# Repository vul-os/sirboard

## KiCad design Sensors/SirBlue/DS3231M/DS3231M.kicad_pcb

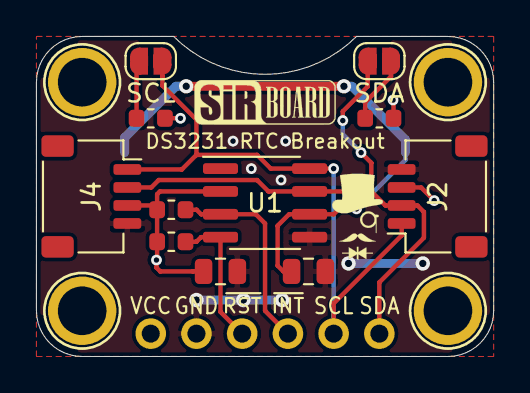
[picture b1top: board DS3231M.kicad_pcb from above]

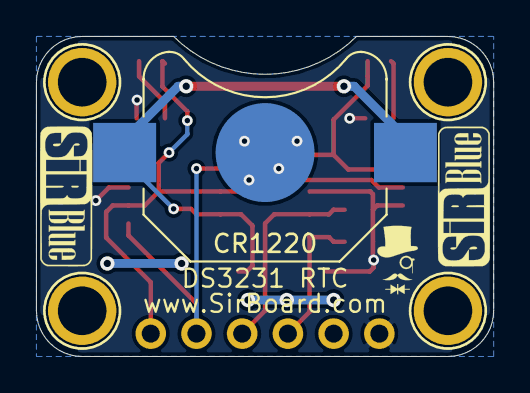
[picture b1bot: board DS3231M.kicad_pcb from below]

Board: 2 copper layers, 25.4 x 17.8 mm, 17 parts (2 on the bottom side), 9 nets.

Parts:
C1: 10uF; C_0805_2012Metric
C2: 1uF; C_0805_2012Metric
CR1220: CR1220; BatteryHolder_Keystone_3000_1x12mm
H1, H2, H3, H4: MountingHole; MountingHole_M2.5_SirBoard
J1: Conn_01x06; PinHeader_1x06_P2.54mm_Vertical
J2, J4: Conn_01x04; JST_SH_SM04B-SRSS-TB_1x04-1MP_P1.00mm_Horizontal
R1, R2: 4.7k; R_0603_1608Metric
R3, R4: 10k; R_0603_1608Metric
SCL: SolderJumper_2_Open; SolderJumper-2_P1.3mm_Open_RoundedPad1.0x1.5mm
SDA: SolderJumper_2_Open; SolderJumper-2_P1.3mm_Open_RoundedPad1.0x1.5mm
U1: DS3231MZ; SOIC-8_3.9x4.9mm_P1.27mm

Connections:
GND: C1.2, C2.2, CR1220.2, J1.2, J2.4, J4.4, U1.5
unnamed: R1.2, SCL.2
unnamed: R2.2, SDA.2
RST: J1.3, R3.2, U1.4
SCL: J1.5, J2.1, J4.1, SCL.1, U1.8
SDA: J1.6, J2.2, J4.2, SDA.1, U1.7
SQW: J1.4, R4.2, U1.3
VBAT: C2.1, CR1220.1, U1.6
VCC: C1.1, J1.1, J2.3, J4.3, R1.1, R2.1, R3.1, R4.1, U1.2

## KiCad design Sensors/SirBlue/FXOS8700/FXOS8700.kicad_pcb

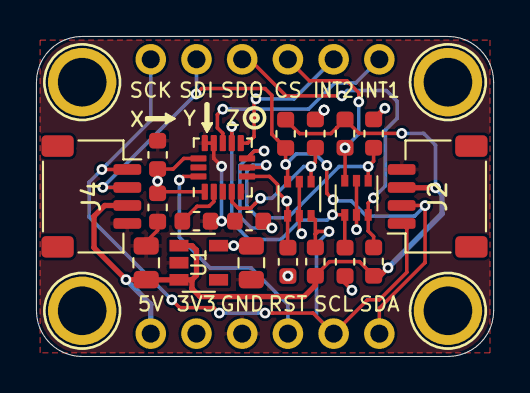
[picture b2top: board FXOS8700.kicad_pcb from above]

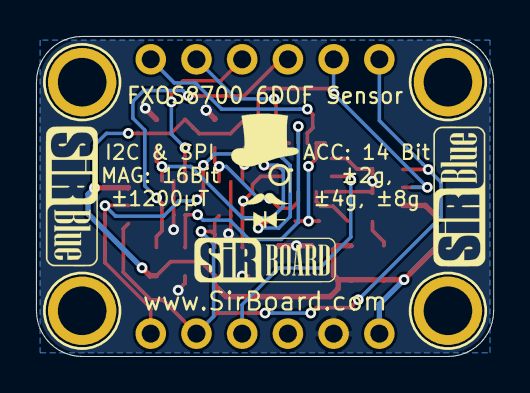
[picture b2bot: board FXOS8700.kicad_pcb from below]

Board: 2 copper layers, 25.4 x 17.8 mm, 26 parts (2 on the bottom side), 16 nets.

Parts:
C1, C4: 10uF; C_0805_2012Metric
C2, C3, C5, C6: 100nF; C_0603_1608Metric
H1, H2, H3, H4: MountingHole; MountingHole_M2.5_SirBoard
J1, J3: Conn_01x06; PinHeader_1x06_P2.54mm_Vertical
J2, J4: Conn_01x04; JST_SH_SM04B-SRSS-TB_1x04-1MP_P1.00mm_Horizontal
Q1, Q2: BSS138DW; SOT-363_SC-70-6
R1, R2, R3, R4, R5, R6, R7, R8: 10K; R_0603_1608Metric
U1: AP2127K-3.3; SOT-23-5
U2: FXOS8700; QFN-COL-16-P=0.5

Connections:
3V3: C3.1, C4.1, C6.1, J1.2, Q1.2, Q1.5, Q2.2, Q2.5, R1.2, R3.2, R5.2, R7.2, U1.5, U2.1, U2.14
5V: C1.1, J1.1, J2.3, J4.3, R2.1, R4.1, R6.1, R8.1, U1.1, U1.3
CS_3V3: Q1.4, R3.1, U2.10
CS_5V: J3.4, Q1.3, R4.2
GND: C1.2, C2.2, C3.2, C4.2, C5.2, C6.2, J1.3, J2.4, J4.4, U1.2, U2.5, U2.12, U2.13
INT1: J3.6, U2.11
INT2: J3.5, U2.9
unnamed: C2.1, U2.2
unnamed: C5.1, U2.8
RST: J1.4, U2.16
SCL_3V3: Q2.1, R5.1, U2.4
SCL_5V: J1.5, J2.1, J3.1, J4.1, Q2.6, R6.2
SDA_3V3: Q2.4, R7.1, U2.6
SDA_5V: J1.6, J2.2, J3.2, J4.2, Q2.3, R8.2
SDO_3V3: Q1.1, R1.1, U2.7
SDO_5V: J3.3, Q1.6, R2.2

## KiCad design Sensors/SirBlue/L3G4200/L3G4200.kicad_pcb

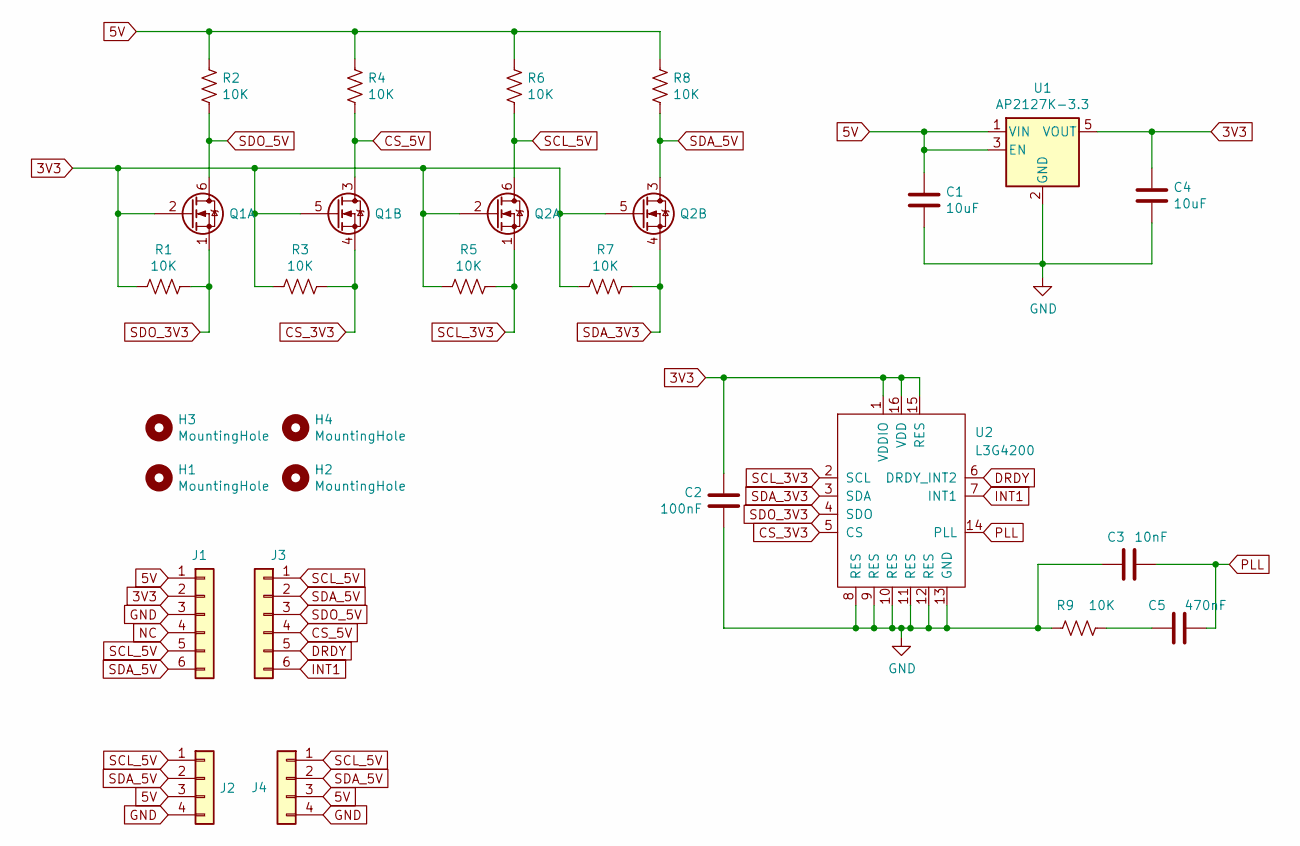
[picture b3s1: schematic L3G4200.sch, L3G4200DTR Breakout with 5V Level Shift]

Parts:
C1, C4: 10uF; C_0805_2012Metric; Part C95841
C2: 100nF; C_0603_1608Metric; Part C42998
C3: 10nF; C_0603_1608Metric; Part C100042
C5: 470nF; C_0603_1608Metric; Part C326968
H1, H2, H3, H4: MountingHole; MountingHole_M2.5_SirBoard
J1, J3: Conn_01x06; PinHeader_1x06_P2.54mm_Vertical
J2, J4: Conn_01x04; SirBlue_Connector; Part C160404
Q1, Q2: BSS138DW; SOT-363_SC-70-6
R1, R2, R3, R4, R5, R6, R7, R8, R9: 10K; R_0603_1608Metric; Part C99198
U1: AP2127K-3.3; SOT-23-5; Part C156285
U2: L3G4200; LGA-16_4x4mm_P0.65mm_LayoutBorder4x4y; Part C26444

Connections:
3V3: C2.1, C4.1, J1.2, Q1.2 (G), Q1.5 (G), Q2.2 (G), Q2.5 (G), R1.2, R3.2, R5.2, R7.2, U1.5 (VOUT), U2.1 (VDDIO), U2.15 (RES), U2.16 (VDD)
5V: C1.1, J1.1, J2.3, J4.3, R2.1, R4.1, R6.1, R8.1, U1.1 (VIN), U1.3 (EN)
CS_3V3: Q1.4 (S), R3.1, U2.5 (CS)
CS_5V: J3.4, Q1.3 (D), R4.2
DRDY: J3.5, U2.6 (DRDY_INT2)
GND: C1.2, C2.2, C3.2, C4.2, J1.3, J2.4, J4.4, R9.2, U1.2 (GND), U2.8 (RES), U2.9 (RES), U2.10 (RES), U2.11 (RES), U2.12 (RES), U2.13 (GND)
INT1: J3.6, U2.7 (INT1)
NC: J1.4
unnamed: C5.2, R9.1
PLL: C3.1, C5.1, U2.14 (PLL)
SCL_3V3: Q2.1 (S), R5.1, U2.2 (SCL)
SCL_5V: J1.5, J2.1, J3.1, J4.1, Q2.6 (D), R6.2
SDA_3V3: Q2.4 (S), R7.1, U2.3 (SDA)
SDA_5V: J1.6, J2.2, J3.2, J4.2, Q2.3 (D), R8.2
SDO_3V3: Q1.1 (S), R1.1, U2.4 (SDO)
SDO_5V: J3.3, Q1.6 (D), R2.2

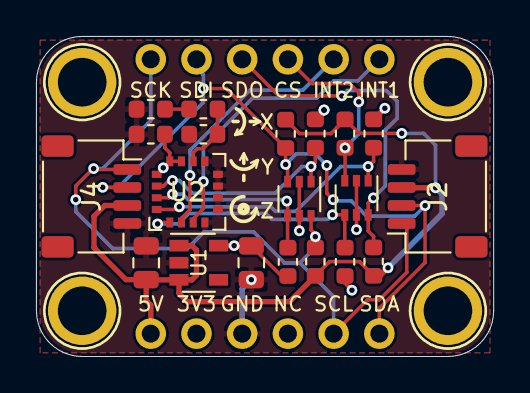
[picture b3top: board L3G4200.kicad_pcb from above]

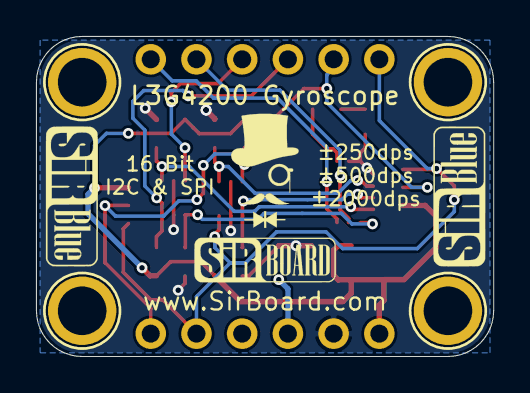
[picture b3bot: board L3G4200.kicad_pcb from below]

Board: 2 copper layers, 25.4 x 17.8 mm, 26 parts (2 on the bottom side), 15 nets.

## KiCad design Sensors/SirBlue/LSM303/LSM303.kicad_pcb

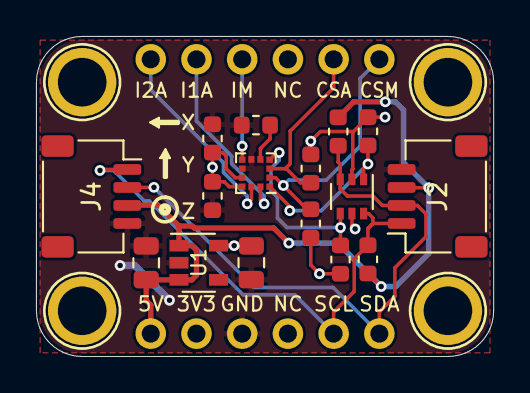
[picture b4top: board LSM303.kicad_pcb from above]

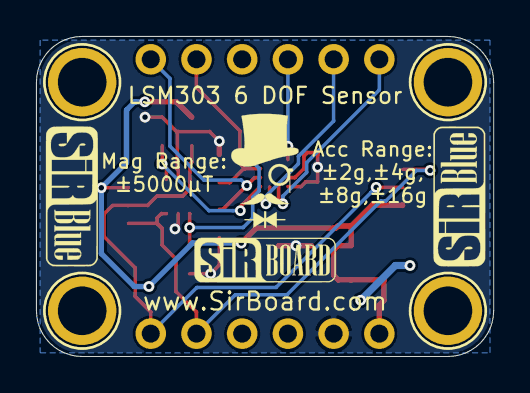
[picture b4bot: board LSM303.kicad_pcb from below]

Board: 2 copper layers, 25.4 x 17.8 mm, 22 parts (2 on the bottom side), 13 nets.

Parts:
C1, C4: 10uF; C_0805_2012Metric
C2: 220nF; C_0603_1608Metric
C3, C5: 100nF; C_0603_1608Metric
H1, H2, H3, H4: MountingHole; MountingHole_M2.5_SirBoard
J1, J3: Conn_01x06; PinHeader_1x06_P2.54mm_Vertical
J2, J4: Conn_01x04; JST_SH_SM04B-SRSS-TB_1x04-1MP_P1.00mm_Horizontal
Q2: BSS138DW; SOT-363_SC-70-6
R1, R2, R5, R6, R7, R8: 10K; R_0603_1608Metric
U1: AP2127K-3.3; SOT-23-5
U2: LSM303AGR; LGA-12_2x2mm_P0.5mm

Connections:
3V3: C3.1, C4.1, C5.1, J1.2, Q2.2, Q2.5, R1.1, R2.1, R5.2, R7.2, U1.5, U2.9, U2.10
5V: C1.1, J1.1, J2.3, J4.3, R6.1, R8.1, U1.1, U1.3
CS_MAG: J3.5, R2.2, U2.3
CS__XL: J3.6, R1.2, U2.2
GND: C1.2, C2.2, C3.2, C4.2, C5.2, J1.3, J2.4, J4.4, U1.2, U2.6, U2.8
INT1_XL: J3.2, U2.12
INT2_XL: J3.1, U2.11
INT_MAG: J3.3, U2.7
unnamed: C2.1, U2.5
SCL_3V3: Q2.1, R5.1, U2.1
SCL_5V: J1.5, J2.1, J4.1, Q2.6, R6.2
SDA_3V3: Q2.4, R7.1, U2.4
SDA_5V: J1.6, J2.2, J4.2, Q2.3, R8.2
